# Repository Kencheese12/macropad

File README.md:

# macropad（みるな！）

4×4（14キー＋EC11ロータリーエンコーダー×2）のマクロパッド。

AIによる補助がどこまで行けるのか検証中

下は確認用

見るんじゃねえって言ったろ！

- MCU: Adafruit KB2040（コンスルー3.5mmで裏面に実装）
- スイッチ: Kailh Choc V2（ホットスワップ CPG135001S30）
- 基板: 86.2 × 86.2 mm、2層、JLCPCB PCBA（裏面実装）
- KiCad 10.0.7

## ブラウザで見る（KiCanvas）

- [基板を見る](https://kicanvas.org/?repo=https%3A%2F%2Fgithub.com%2FKencheese12%2Fmacropad%2Fblob%2Fmain%2Ffocuspad.kicad_pcb)
- [回路図を見る](https://kicanvas.org/?repo=https%3A%2F%2Fgithub.com%2FKencheese12%2Fmacropad%2Fblob%2Fmain%2Ffocuspad.kicad_sch)

## ファイル構成

- `focuspad.kicad_pro` / `.kicad_sch` / `.kicad_pcb`: KiCadプロジェクト
- `focuspad.pretty/`: 自作フットプリント
- `fp-lib-table`: プロジェクト固有のフットプリントライブラリ登録
- `make_schematic.py`: 回路図生成スクリプト
- `place_focuspad.py`: 部品配置スクリプト
- `docs/`: 製作手順書・自動配線手順書# macropad

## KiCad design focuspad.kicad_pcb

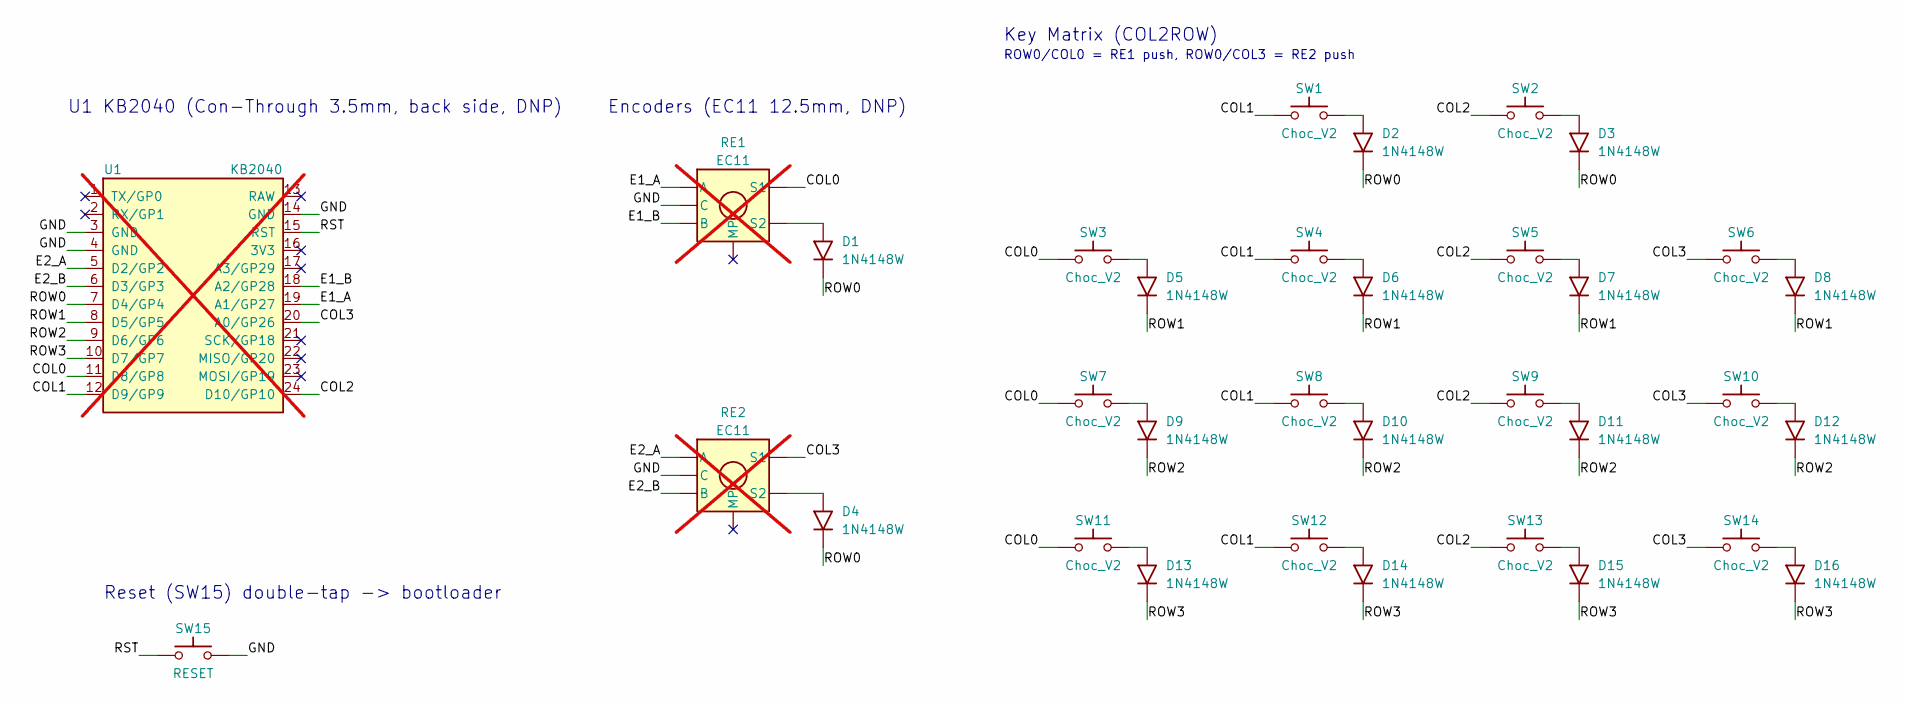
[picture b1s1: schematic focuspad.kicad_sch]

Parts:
D1, D2, D3, D4, D5, D6, D7, D8, D9, D10, D11, D12, D13, D14, D15, D16: 1N4148W; D_SOD-123; LCSC C81598
RE1, RE2: EC11; EC11_Switch_Vertical; not fitted
SW1, SW2, SW3, SW4, SW5, SW6, SW7, SW8, SW9, SW10, SW11, SW12, SW13, SW14: Choc_V2; SW_Choc_V2_Hotswap; LCSC C5333465
SW15: RESET; SW_TS-1187A; LCSC C318884
U1: KB2040; KB2040_ConThrough; not fitted

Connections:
/COL0: RE1.S1, SW3.1, SW7.1, SW11.1, U1.11 (D8/GP8)
/COL1: SW1.1, SW4.1, SW8.1, SW12.1, U1.12 (D9/GP9)
/COL2: SW2.1, SW5.1, SW9.1, SW13.1, U1.24 (D10/GP10)
/COL3: RE2.S1, SW6.1, SW10.1, SW14.1, U1.20 (A0/GP26)
/E1_A: RE1.A, U1.19 (A1/GP27)
/E1_B: RE1.B, U1.18 (A2/GP28)
/E2_A: RE2.A, U1.5 (D2/GP2)
/E2_B: RE2.B, U1.6 (D3/GP3)
/GND: RE1.C, RE2.C, SW15.2, U1.3 (GND), U1.4 (GND), U1.14 (GND)
/ROW0: D1.1 (K), D2.1 (K), D3.1 (K), D4.1 (K), U1.7 (D4/GP4)
/ROW1: D5.1 (K), D6.1 (K), D7.1 (K), D8.1 (K), U1.8 (D5/GP5)
/ROW2: D9.1 (K), D10.1 (K), D11.1 (K), D12.1 (K), U1.9 (D6/GP6)
/ROW3: D13.1 (K), D14.1 (K), D15.1 (K), D16.1 (K), U1.10 (D7/GP7)
/RST: SW15.1, U1.15 (RST)
unnamed: D1.2 (A), RE1.S2
unnamed: D2.2 (A), SW1.2
unnamed: D3.2 (A), SW2.2
unnamed: D4.2 (A), RE2.S2
unnamed: D5.2 (A), SW3.2
unnamed: D6.2 (A), SW4.2
unnamed: D7.2 (A), SW5.2
unnamed: D8.2 (A), SW6.2
unnamed: D9.2 (A), SW7.2
unnamed: D10.2 (A), SW8.2
unnamed: D11.2 (A), SW9.2
unnamed: D12.2 (A), SW10.2
unnamed: D13.2 (A), SW11.2
unnamed: D14.2 (A), SW12.2
unnamed: D15.2 (A), SW13.2
unnamed: D16.2 (A), SW14.2

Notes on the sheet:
Key Matrix (COL2ROW)
Reset (SW15) double-tap -> bootloader
Encoders (EC11 12.5mm, DNP)
ROW0/COL0 = RE1 push, ROW0/COL3 = RE2 push
U1 KB2040 (Con-Through 3.5mm, back side, DNP)

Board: 2 copper layers, 38 parts (31 on the bottom side), 30 nets, no tracks yet.

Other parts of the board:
H**: M2; MountingHole_M2
H**#2, H**#3, H**#4: M2; MountingHole_M2
